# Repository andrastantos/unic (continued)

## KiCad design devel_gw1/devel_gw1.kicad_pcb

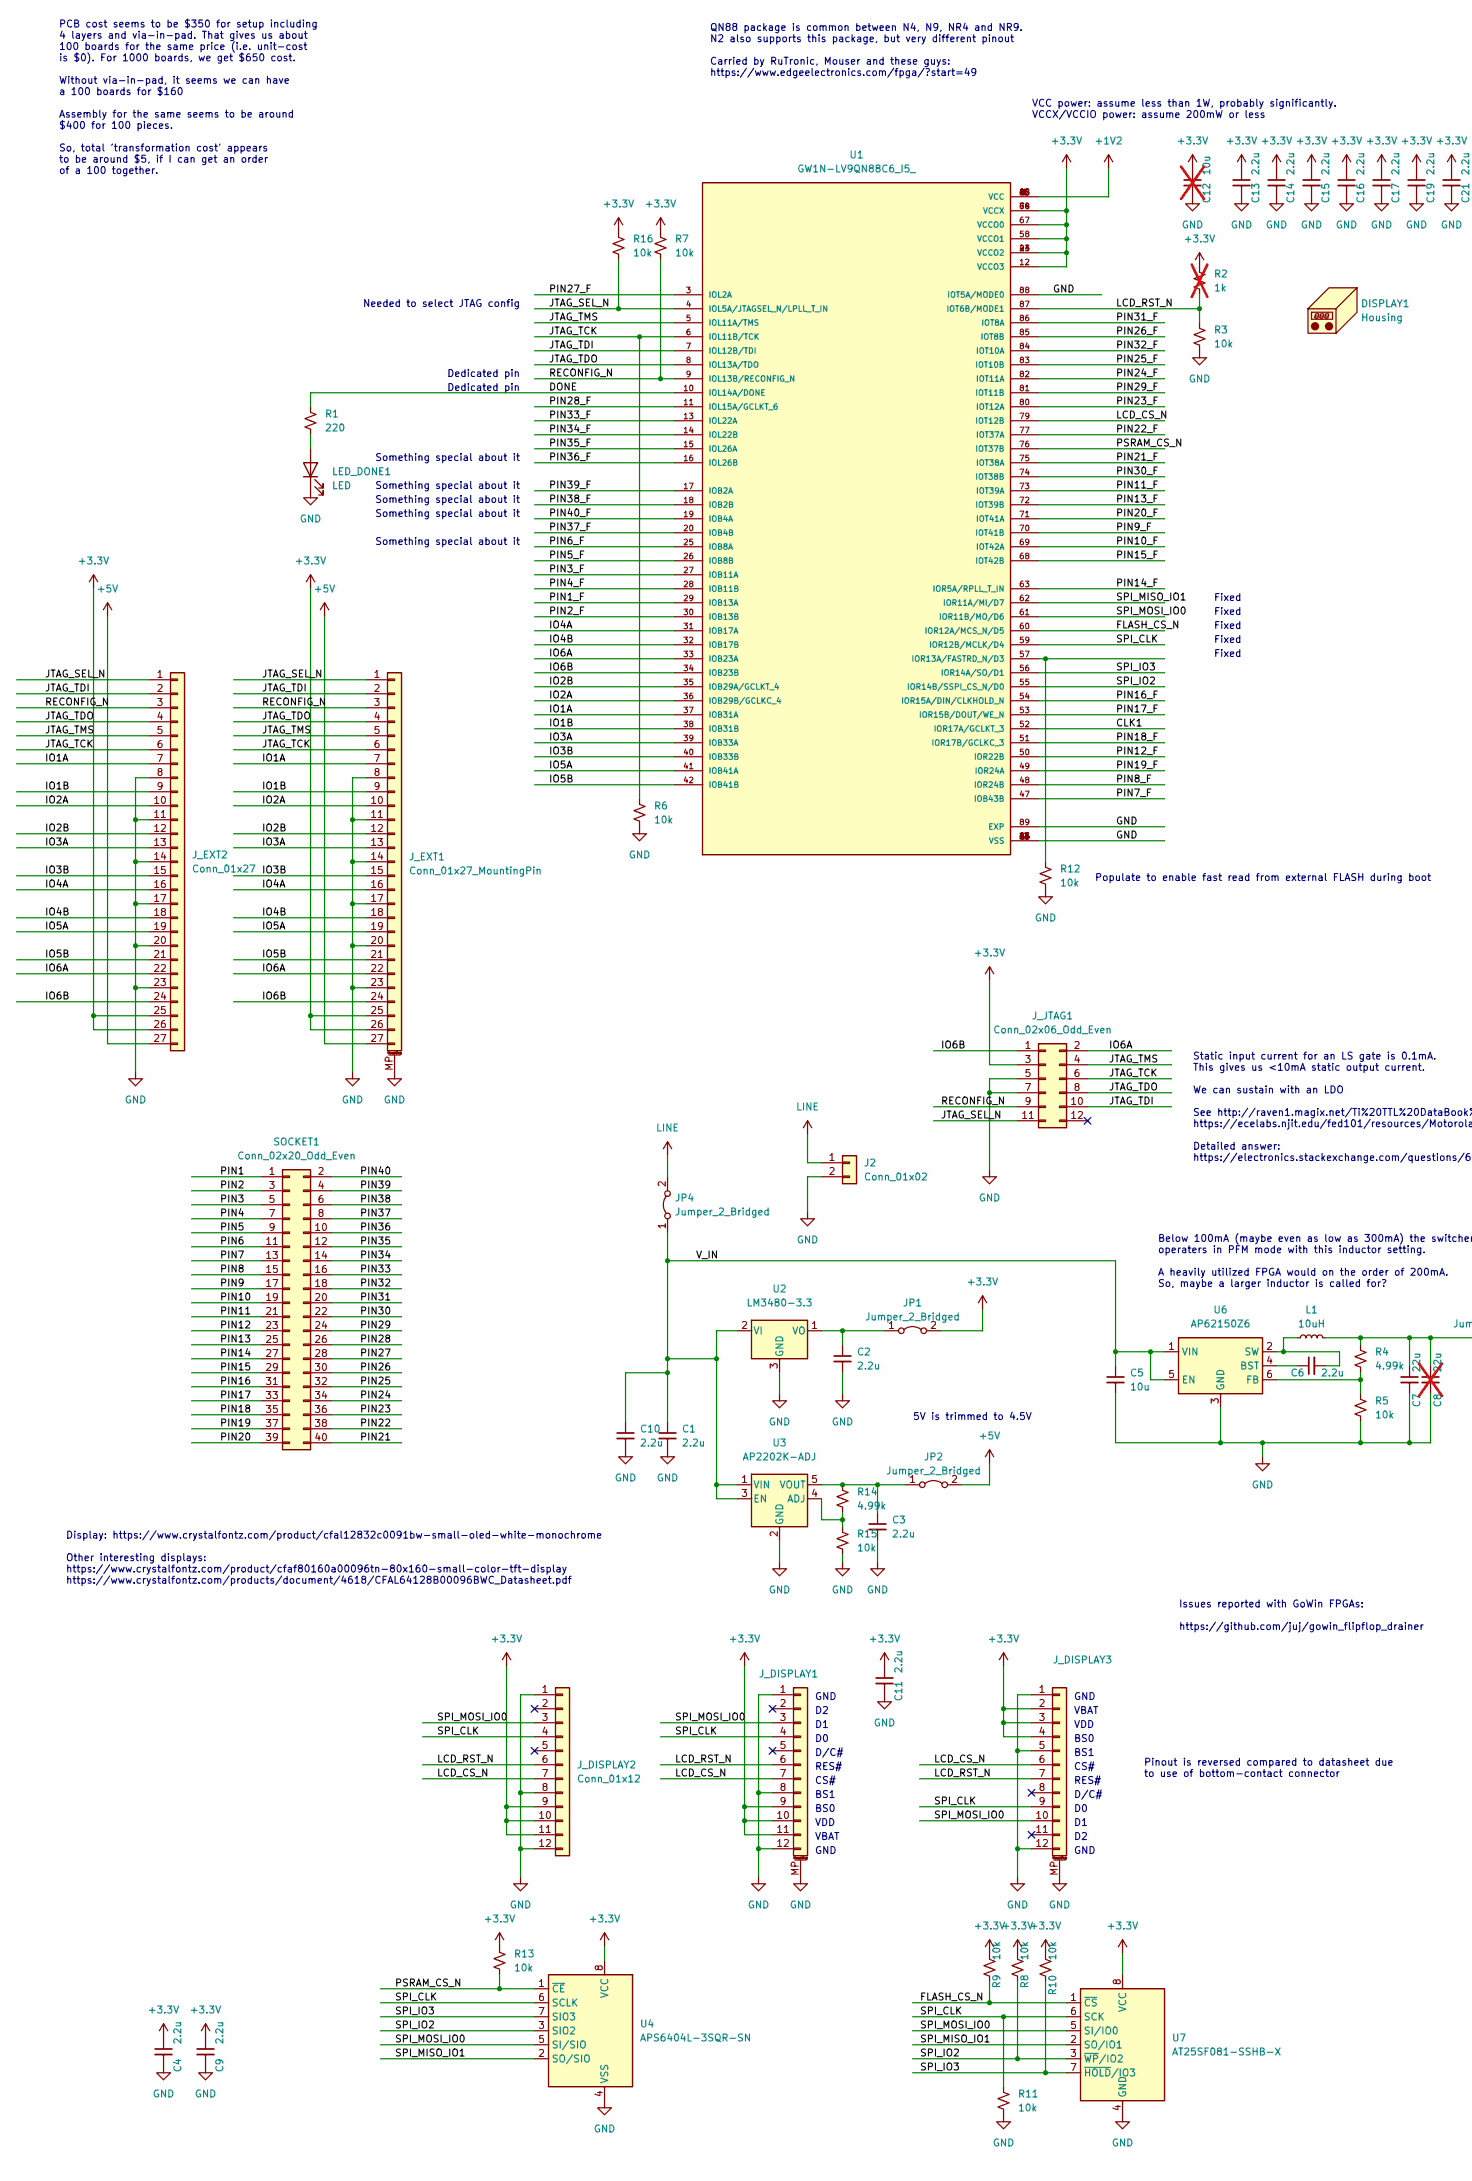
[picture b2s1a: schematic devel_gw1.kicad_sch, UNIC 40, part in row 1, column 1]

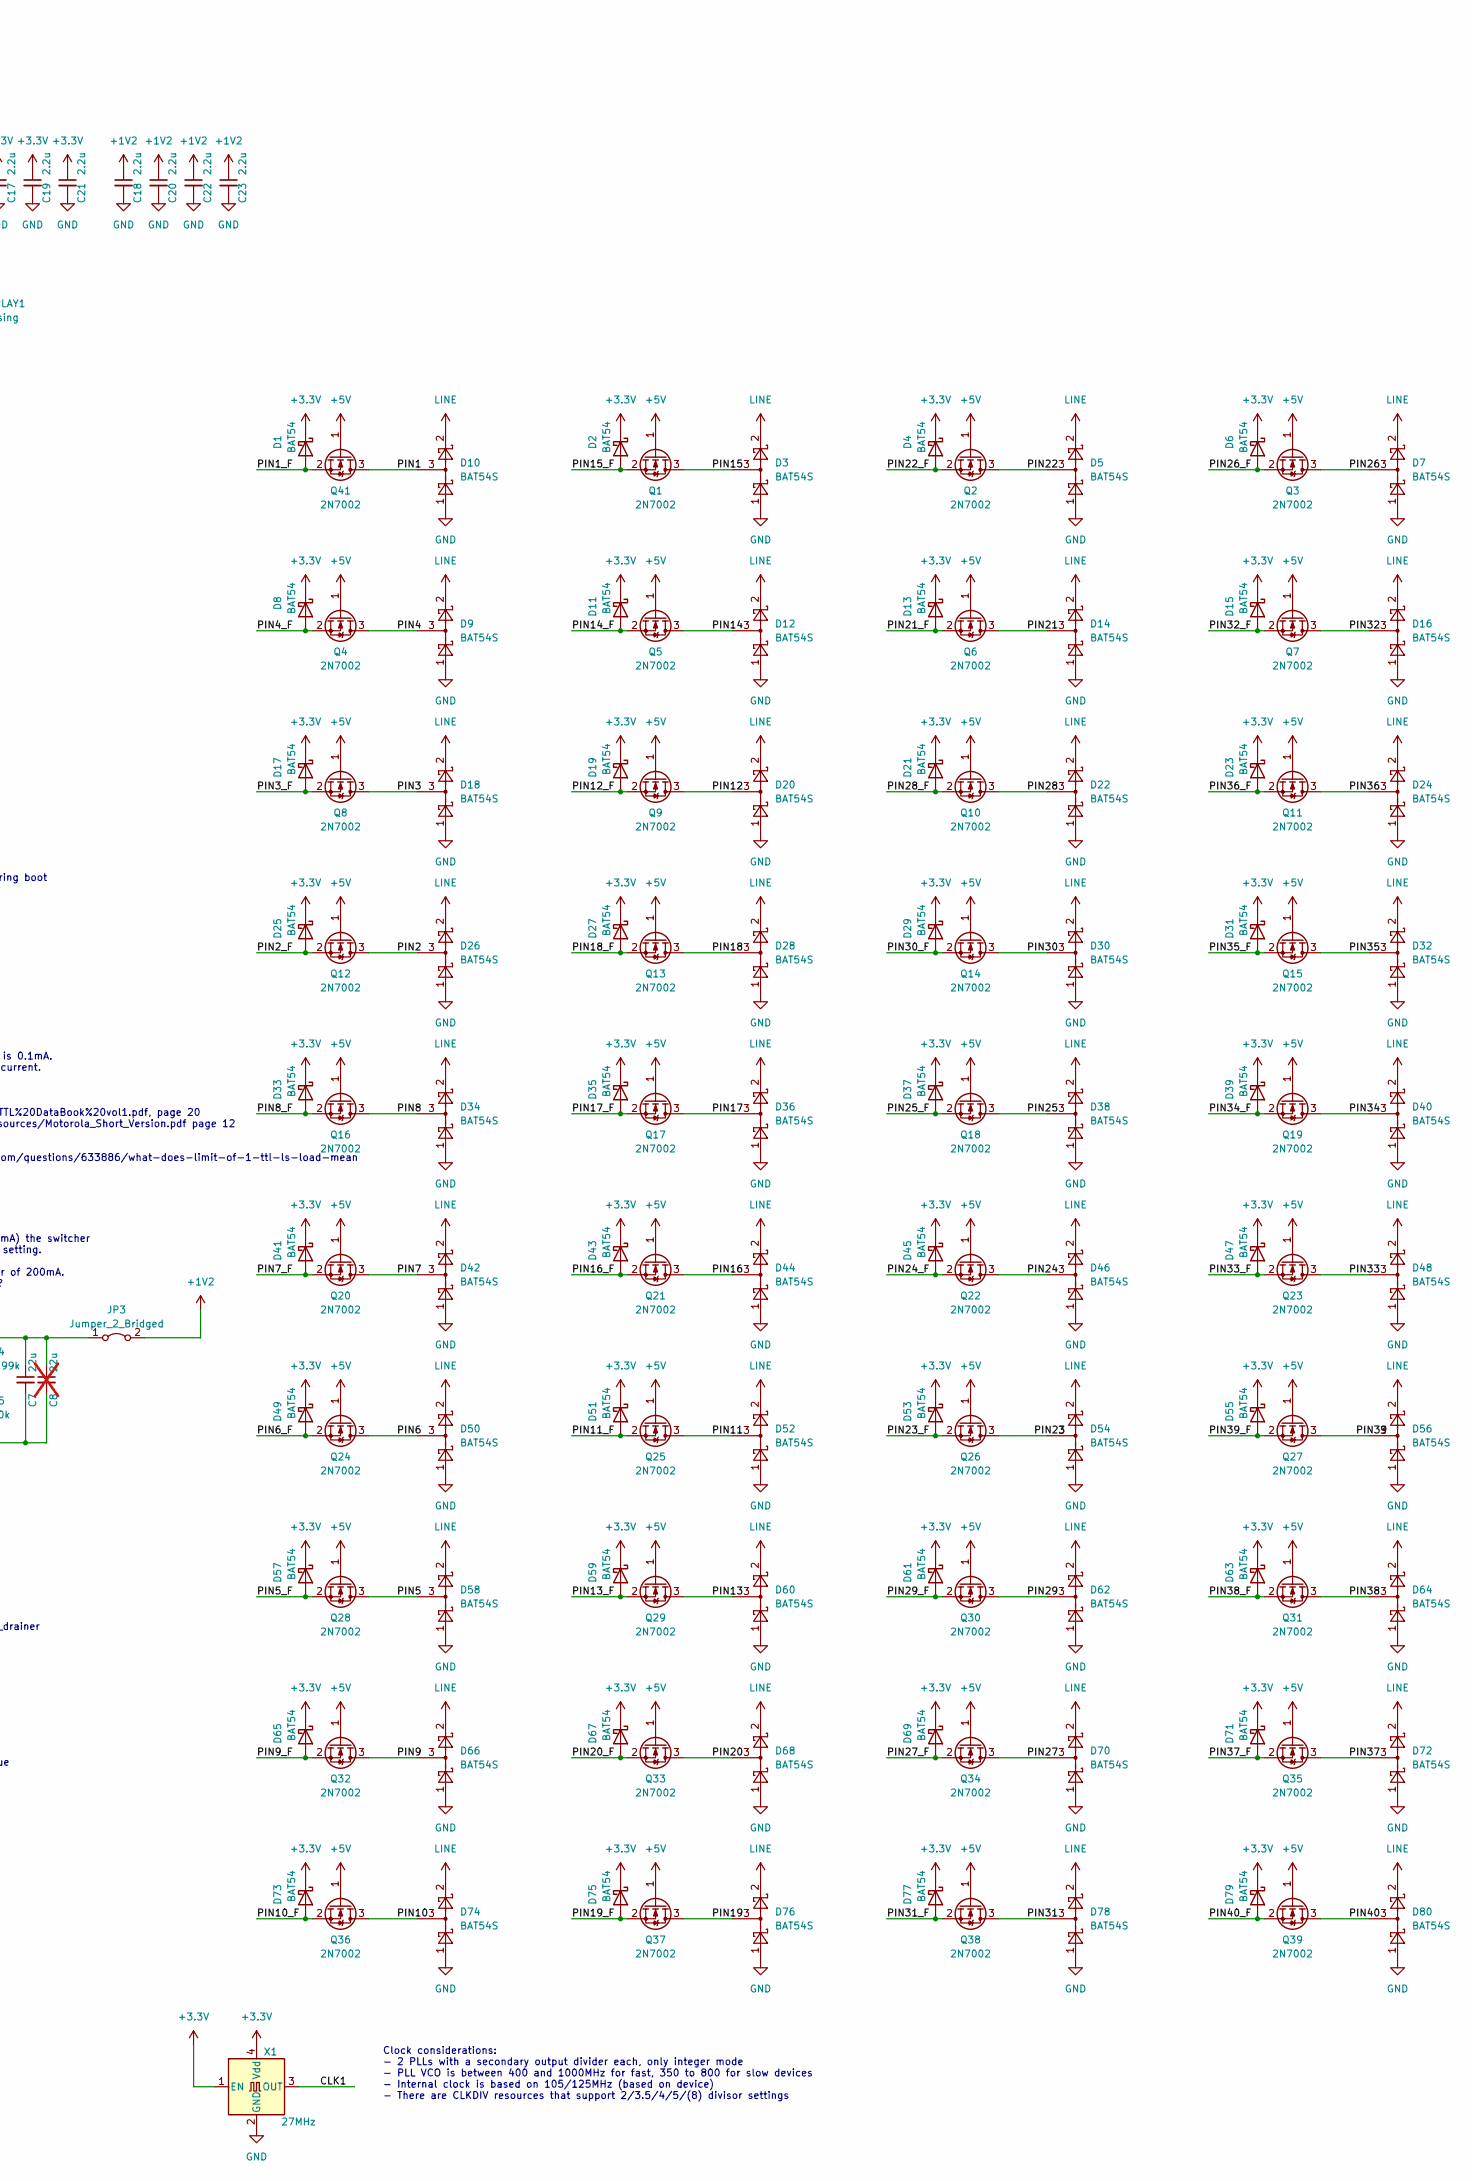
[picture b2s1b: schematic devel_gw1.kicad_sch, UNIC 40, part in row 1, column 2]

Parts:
C1, C2, C3, C4, C6, C9, C10, C11, C13, C14, C15, C16, C17, C18, C19, C20, C21, C22, C23: 2.2u; C_0402_1005Metric_Pad0.74x0.62mm_HandSolder
C5: 10u; C_0805_2012Metric_Pad1.18x1.45mm_HandSolder
C7: 22u; C_0805_2012Metric_Pad1.18x1.45mm_HandSolder
C8: 22u; C_0805_2012Metric_Pad1.18x1.45mm_HandSolder; not fitted
C12: 10u; C_0805_2012Metric_Pad1.18x1.45mm_HandSolder; not fitted
D1, D2, D4, D6, D8, D11, D13, D15, D17, D19, D21, D23, D25, D27, D29, D31, D33, D35, D37, D39, D41, D43, D45, D47, D49, D51, D53, D55, D57, D59, D61, D63, D65, D67, D69, D71, D73, D75, D77, D79: BAT54; SOT-23
D3, D5, D7, D9, D10, D12, D14, D16, D18, D20, D22, D24, D26, D28, D30, D32, D34, D36, D38, D40, D42, D44, D46, D48, D50, D52, D54, D56, D58, D60, D62, D64, D66, D68, D70, D72, D74, D76, D78, D80: BAT54S; SOT-23
DISPLAY1: Housing; CFAL12832C-0091B-W_A
J2: Conn_01x02; PinHeader_1x02_P2.54mm_Vertical
JP1, JP2, JP3, JP4: Jumper_2_Bridged; PinHeader_1x02_P2.54mm_Vertical
J_DISPLAY1: Conn_01x12_MountingPin; CF4212FH0R0-05-NH
J_DISPLAY2: Conn_01x12; PinHeader_1x12_P2.54mm_Vertical
J_DISPLAY3: Conn_01x12_MountingPin; CF31121D0R0-05-NH
J_EXT1: Conn_01x27_MountingPin; Molex_502598-2793_2Rows-23P~0.60mm_Horizontal
J_EXT2: Conn_01x27; PinHeader_2x14_P2.54mm_Vertical
J_JTAG1: Conn_02x06_Odd_Even; PinHeader_2x06_P1.27mm_Vertical_SMD
L1: 10uH; L_1008_2520Metric_Pad1.43x2.20mm_HandSolder
LED_DONE1: LED; LED_0402_1005Metric_Pad0.77x0.64mm_HandSolder
Q1, Q2, Q3, Q4, Q5, Q6, Q7, Q8, Q9, Q10, Q11, Q12, Q13, Q14, Q15, Q16, Q17, Q18, Q19, Q20, Q21, Q22, Q23, Q24, Q25, Q26, Q27, Q28, Q29, Q30, Q31, Q32, Q33, Q34, Q35, Q36, Q37, Q38, Q39, Q41: 2N7002; SOT-23
R1: 220; R_0402_1005Metric_Pad0.72x0.64mm_HandSolder
R2: 1k; R_0402_1005Metric_Pad0.72x0.64mm_HandSolder; not fitted
R3, R5, R6, R7, R8, R9, R10, R11, R12, R13, R15, R16: 10k; R_0402_1005Metric_Pad0.72x0.64mm_HandSolder
R4, R14: 4.99k; R_0402_1005Metric_Pad0.72x0.64mm_HandSolder
SOCKET1: Conn_02x20_Odd_Even; PinSocket_2x20_P2.54mm_Horizontal
U1: GW1N-LV9QN88C6_I5_; QFN40P1000X1000X95-89N_hand_solder; PARTREV UG103-2.3E
U2: LM3480-3.3; SOT-23
U3: AP2202K-ADJ; SOT-23-5
U4: APS6404L-3SQR-SN; SOIC-8_3.9x4.9mm_P1.27mm
U6: AP62150Z6; SOT-563
U7: AT25SF081-SSHB-X; SOIC-8_3.9x4.9mm_P1.27mm
X1: 27MHz; Oscillator_SMD_Abracon_ASE-4Pin_3.2x2.5mm

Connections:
+1V2: C18.1, C20.1, C22.1, C23.1, JP3.2 (B), U1.1 (VCC), U1.22 (VCC), U1.45 (VCC), U1.66 (VCC)
+3V3: C4.1, C9.1, C11.1, C12.1, C13.1, C14.1, C15.1, C16.1, C17.1, C19.1, C21.1, D1.3 (K), D2.3 (K), D4.3 (K), D6.3 (K), D8.3 (K), D11.3 (K), D13.3 (K), D15.3 (K), D17.3 (K), D19.3 (K), D21.3 (K), D23.3 (K), D25.3 (K), D27.3 (K), D29.3 (K), D31.3 (K), D33.3 (K), D35.3 (K), D37.3 (K), D39.3 (K), D41.3 (K), D43.3 (K), D45.3 (K), D47.3 (K), D49.3 (K), D51.3 (K), D53.3 (K), D55.3 (K), D57.3 (K), D59.3 (K), D61.3 (K), D63.3 (K), D65.3 (K), D67.3 (K), D69.3 (K), D71.3 (K), D73.3 (K), D75.3 (K), D77.3 (K), D79.3 (K), JP1.2 (B), J_DISPLAY1.9, J_DISPLAY1.10, J_DISPLAY1.11, J_DISPLAY2.9, J_DISPLAY2.10, J_DISPLAY2.11, J_DISPLAY3.2, J_DISPLAY3.3, J_DISPLAY3.4, J_EXT1.25, J_EXT1.26, J_EXT2.25, J_EXT2.26, J_JTAG1.3, R2.1, R7.1, R8.1, R9.1, R10.1, R13.1, R16.1, U1.12 (VCCO3), U1.23 (VCCO2), U1.44 (VCCO2), U1.58 (VCCO1), U1.64 (VCCX), U1.67 (VCCO0), U1.78 (VCCX), U4.8 (VCC), U7.8 (VCC), X1.1 (EN), X1.4 (Vdd)
+5V: JP2.2 (B), J_EXT1.27, J_EXT2.27, Q1.1 (G), Q2.1 (G), Q3.1 (G), Q4.1 (G), Q5.1 (G), Q6.1 (G), Q7.1 (G), Q8.1 (G), Q9.1 (G), Q10.1 (G), Q11.1 (G), Q12.1 (G), Q13.1 (G), Q14.1 (G), Q15.1 (G), Q16.1 (G), Q17.1 (G), Q18.1 (G), Q19.1 (G), Q20.1 (G), Q21.1 (G), Q22.1 (G), Q23.1 (G), Q24.1 (G), Q25.1 (G), Q26.1 (G), Q27.1 (G), Q28.1 (G), Q29.1 (G), Q30.1 (G), Q31.1 (G), Q32.1 (G), Q33.1 (G), Q34.1 (G), Q35.1 (G), Q36.1 (G), Q37.1 (G), Q38.1 (G), Q39.1 (G), Q41.1 (G)
/CLK1: U1.52 (IOR17A/GCLKT_3), X1.3 (OUT)
/DONE: R1.1, U1.10 (IOL14A/DONE)
/FLASH_CS_N: R9.2, U1.60 (IOR12A/MCS_N/D5), U7.1 (~CS)
/IO1A: J_EXT1.7, J_EXT2.7, U1.37 (IOB31A)
/IO1B: J_EXT1.9, J_EXT2.9, U1.38 (IOB31B)
/IO2A: J_EXT1.10, J_EXT2.10, U1.36 (IOB29B/GCLKC_4)
/IO2B: J_EXT1.12, J_EXT2.12, U1.35 (IOB29A/GCLKT_4)
/IO3A: J_EXT1.13, J_EXT2.13, U1.39 (IOB33A)
/IO3B: J_EXT1.15, J_EXT2.15, U1.40 (IOB33B)
/IO4A: J_EXT1.16, J_EXT2.16, U1.31 (IOB17A)
/IO4B: J_EXT1.18, J_EXT2.18, U1.32 (IOB17B)
/IO5A: J_EXT1.19, J_EXT2.19, U1.41 (IOB41A)
/IO5B: J_EXT1.21, J_EXT2.21, U1.42 (IOB41B)
/IO6A: J_EXT1.22, J_EXT2.22, J_JTAG1.2, U1.33 (IOB23A)
/IO6B: J_EXT1.24, J_EXT2.24, J_JTAG1.1, U1.34 (IOB23B)
/JTAG_SEL_N: J_EXT1.1, J_EXT2.1, J_JTAG1.11, R16.2, U1.4 (IOL5A/JTAGSEL_N/LPLL_T_IN)
/JTAG_TCK: J_EXT1.6, J_EXT2.6, J_JTAG1.6, R6.1, U1.6 (IOL11B/TCK)
/JTAG_TDI: J_EXT1.2, J_EXT2.2, J_JTAG1.10, U1.7 (IOL12B/TDI)
/JTAG_TDO: J_EXT1.4, J_EXT2.4, J_JTAG1.8, U1.8 (IOL13A/TDO)
/JTAG_TMS: J_EXT1.5, J_EXT2.5, J_JTAG1.4, U1.5 (IOL11A/TMS)
/LCD_CS_N: J_DISPLAY1.7, J_DISPLAY2.7, J_DISPLAY3.6, U1.79 (IOT12B)
/LCD_RST_N: J_DISPLAY1.6, J_DISPLAY2.6, J_DISPLAY3.7, R2.2, R3.1, U1.87 (IOT6B/MODE1)
/PIN1: D10.3, Q41.3 (D), SOCKET1.1
/PIN1_F: D1.1 (A), Q41.2 (S), U1.29 (IOB13A)
/PIN2: D26.3, Q12.3 (D), SOCKET1.3
/PIN2_F: D25.1 (A), Q12.2 (S), U1.30 (IOB13B)
/PIN3: D18.3, Q8.3 (D), SOCKET1.5
/PIN3_F: D17.1 (A), Q8.2 (S), U1.27 (IOB11A)
/PIN4: D9.3, Q4.3 (D), SOCKET1.7
/PIN4_F: D8.1 (A), Q4.2 (S), U1.28 (IOB11B)
/PIN5: D58.3, Q28.3 (D), SOCKET1.9
/PIN5_F: D57.1 (A), Q28.2 (S), U1.26 (IOB8B)
/PIN6: D50.3, Q24.3 (D), SOCKET1.11
/PIN6_F: D49.1 (A), Q24.2 (S), U1.25 (IOB8A)
/PIN7: D42.3, Q20.3 (D), SOCKET1.13
/PIN7_F: D41.1 (A), Q20.2 (S), U1.47 (IOB43B)
/PIN8: D34.3, Q16.3 (D), SOCKET1.15
/PIN8_F: D33.1 (A), Q16.2 (S), U1.48 (IOR24B)
/PIN9: D66.3, Q32.3 (D), SOCKET1.17
/PIN9_F: D65.1 (A), Q32.2 (S), U1.70 (IOT41B)
/PIN10: D74.3, Q36.3 (D), SOCKET1.19
/PIN10_F: D73.1 (A), Q36.2 (S), U1.69 (IOT42A)
/PIN11: D52.3, Q25.3 (D), SOCKET1.21
/PIN11_F: D51.1 (A), Q25.2 (S), U1.73 (IOT39A)
/PIN12: D20.3, Q9.3 (D), SOCKET1.23
/PIN12_F: D19.1 (A), Q9.2 (S), U1.50 (IOR22B)
/PIN13: D60.3, Q29.3 (D), SOCKET1.25
/PIN13_F: D59.1 (A), Q29.2 (S), U1.72 (IOT39B)
/PIN14: D12.3, Q5.3 (D), SOCKET1.27
/PIN14_F: D11.1 (A), Q5.2 (S), U1.63 (IOR5A/RPLL_T_IN)
/PIN15: D3.3, Q1.3 (D), SOCKET1.29
/PIN15_F: D2.1 (A), Q1.2 (S), U1.68 (IOT42B)
/PIN16: D44.3, Q21.3 (D), SOCKET1.31
/PIN16_F: D43.1 (A), Q21.2 (S), U1.54 (IOR15A/DIN/CLKHOLD_N)
/PIN17: D36.3, Q17.3 (D), SOCKET1.33
/PIN17_F: D35.1 (A), Q17.2 (S), U1.53 (IOR15B/DOUT/WE_N)
/PIN18: D28.3, Q13.3 (D), SOCKET1.35
/PIN18_F: D27.1 (A), Q13.2 (S), U1.51 (IOR17B/GCLKC_3)
/PIN19: D76.3, Q37.3 (D), SOCKET1.37
/PIN19_F: D75.1 (A), Q37.2 (S), U1.49 (IOR24A)
/PIN20: D68.3, Q33.3 (D), SOCKET1.39
/PIN20_F: D67.1 (A), Q33.2 (S), U1.71 (IOT41A)
/PIN21: D14.3, Q6.3 (D), SOCKET1.40
/PIN21_F: D13.1 (A), Q6.2 (S), U1.75 (IOT38A)
/PIN22: D5.3, Q2.3 (D), SOCKET1.38
/PIN22_F: D4.1 (A), Q2.2 (S), U1.77 (IOT37A)
/PIN23: D54.3, Q26.3 (D), SOCKET1.36
/PIN23_F: D53.1 (A), Q26.2 (S), U1.80 (IOT12A)
/PIN24: D46.3, Q22.3 (D), SOCKET1.34
/PIN24_F: D45.1 (A), Q22.2 (S), U1.82 (IOT11A)
/PIN25: D38.3, Q18.3 (D), SOCKET1.32
/PIN25_F: D37.1 (A), Q18.2 (S), U1.83 (IOT10B)
/PIN26: D7.3, Q3.3 (D), SOCKET1.30
/PIN26_F: D6.1 (A), Q3.2 (S), U1.85 (IOT8B)
/PIN27: D70.3, Q34.3 (D), SOCKET1.28
/PIN27_F: D69.1 (A), Q34.2 (S), U1.3 (IOL2A)
/PIN28: D22.3, Q10.3 (D), SOCKET1.26
/PIN28_F: D21.1 (A), Q10.2 (S), U1.11 (IOL15A/GCLKT_6)
/PIN29: D62.3, Q30.3 (D), SOCKET1.24
/PIN29_F: D61.1 (A), Q30.2 (S), U1.81 (IOT11B)
/PIN30: D30.3, Q14.3 (D), SOCKET1.22
/PIN30_F: D29.1 (A), Q14.2 (S), U1.74 (IOT38B)
/PIN31: D78.3, Q38.3 (D), SOCKET1.20
/PIN31_F: D77.1 (A), Q38.2 (S), U1.86 (IOT8A)
/PIN32: D16.3, Q7.3 (D), SOCKET1.18
/PIN32_F: D15.1 (A), Q7.2 (S), U1.84 (IOT10A)
/PIN33: D48.3, Q23.3 (D), SOCKET1.16
/PIN33_F: D47.1 (A), Q23.2 (S), U1.13 (IOL22A)
/PIN34: D40.3, Q19.3 (D), SOCKET1.14
/PIN34_F: D39.1 (A), Q19.2 (S), U1.14 (IOL22B)
/PIN35: D32.3, Q15.3 (D), SOCKET1.12
/PIN35_F: D31.1 (A), Q15.2 (S), U1.15 (IOL26A)
/PIN36: D24.3, Q11.3 (D), SOCKET1.10
/PIN36_F: D23.1 (A), Q11.2 (S), U1.16 (IOL26B)
/PIN37: D72.3, Q35.3 (D), SOCKET1.8
/PIN37_F: D71.1 (A), Q35.2 (S), U1.20 (IOB4B)
/PIN38: D64.3, Q31.3 (D), SOCKET1.6
/PIN38_F: D63.1 (A), Q31.2 (S), U1.18 (IOB2B)
/PIN39: D56.3, Q27.3 (D), SOCKET1.4
/PIN39_F: D55.1 (A), Q27.2 (S), U1.17 (IOB2A)
/PIN40: D80.3, Q39.3 (D), SOCKET1.2
/PIN40_F: D79.1 (A), Q39.2 (S), U1.19 (IOB4A)
/PSRAM_CS_N: R13.2, U1.76 (IOT37B), U4.1 (~CE)
/RECONFIG_N: J_EXT1.3, J_EXT2.3, J_JTAG1.9, R7.2, U1.9 (IOL13B/RECONFIG_N)
/SPI_CLK: J_DISPLAY1.4, J_DISPLAY2.4, J_DISPLAY3.9, R11.1, U1.59 (IOR12B/MCLK/D4), U4.6 (SCLK), U7.6 (SCK)
/SPI_IO2: R8.2, U1.55 (IOR14B/SSPI_CS_N/D0), U4.3 (SIO2), U7.3 (~WP/IO2)
/SPI_IO3: R10.2, U1.56 (IOR14A/SO/D1), U4.7 (SIO3), U7.7 (~HOLD/IO3)
/SPI_MISO_IO1: U1.62 (IOR11A/MI/D7), U4.2 (SO/SIO), U7.2 (SO/IO1)
/SPI_MOSI_IO0: J_DISPLAY1.3, J_DISPLAY2.3, J_DISPLAY3.10, U1.61 (IOR11B/MO/D6), U4.5 (SI/SIO), U7.5 (SI/IO0)
/V_IN: C1.1, C5.1, C10.1, JP4.1 (A), U2.2 (VI), U3.1 (VIN), U3.3 (EN), U6.1 (VIN), U6.5 (EN)
GND: C1.2, C2.2, C3.2, C4.2, C5.2, C7.2, C8.2, C9.2, C10.2, C11.2, C12.2, C13.2, C14.2, C15.2, C16.2, C17.2, C18.2, C19.2, C20.2, C21.2, C22.2, C23.2, D3.1, D5.1, D7.1, D9.1, D10.1, D12.1, D14.1, D16.1, D18.1, D20.1, D22.1, D24.1, D26.1, D28.1, D30.1, D32.1, D34.1, D36.1, D38.1, D40.1, D42.1, D44.1, D46.1, D48.1, D50.1, D52.1, D54.1, D56.1, D58.1, D60.1, D62.1, D64.1, D66.1, D68.1, D70.1, D72.1, D74.1, D76.1, D78.1, D80.1, J2.2, J_DISPLAY1.1, J_DISPLAY1.8, J_DISPLAY1.12, J_DISPLAY1.MP (MountPin), J_DISPLAY2.1, J_DISPLAY2.8, J_DISPLAY2.12, J_DISPLAY3.1, J_DISPLAY3.5, J_DISPLAY3.12, J_DISPLAY3.MP (MountPin), J_EXT1.8, J_EXT1.11, J_EXT1.14, J_EXT1.17, J_EXT1.20, J_EXT1.23, J_EXT1.MP (MountPin), J_EXT2.8, J_EXT2.11, J_EXT2.14, J_EXT2.17, J_EXT2.20, J_EXT2.23, J_JTAG1.5, J_JTAG1.7, LED_DONE1.1 (K), R3.2, R5.2, R6.2, R11.2, R12.2, R15.2, U1.2 (VSS), U1.21 (VSS), U1.24 (VSS), U1.43 (VSS), U1.46 (VSS), U1.65 (VSS), U1.88 (IOT5A/MODE0), U1.89 (EXP), U2.3 (GND), U3.2 (GND), U4.4 (VSS), U6.3 (GND), U7.4 (GND), X1.2 (GND)
LINE: D3.2, D5.2, D7.2, D9.2, D10.2, D12.2, D14.2, D16.2, D18.2, D20.2, D22.2, D24.2, D26.2, D28.2, D30.2, D32.2, D34.2, D36.2, D38.2, D40.2, D42.2, D44.2, D46.2, D48.2, D50.2, D52.2, D54.2, D56.2, D58.2, D60.2, D62.2, D64.2, D66.2, D68.2, D70.2, D72.2, D74.2, D76.2, D78.2, D80.2, J2.1, JP4.2 (B)
unnamed: C2.1, JP1.1 (A), U2.1 (VO)
unnamed: C3.1, JP2.1 (A), R14.1, U3.5 (VOUT)
unnamed: C7.1, C8.1, JP3.1 (A), L1.2, R4.1
unnamed: LED_DONE1.2 (A), R1.2
unnamed: R12.1, U1.57 (IOR13A/FASTRD_N/D3)
unnamed: R14.2, R15.1, U3.4 (ADJ)
unnamed: C6.1, U6.4 (BST)
unnamed: R4.2, R5.1, U6.6 (FB)
unnamed: C6.2, L1.1, U6.2 (SW)

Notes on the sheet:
BS0
Issues reported with GoWin FPGAs: https://github.com/juj/gowin_flipflop_drainer
D/C#
Populate to enable fast read from external FLASH during boot
VBAT
Fixed
Something special about it
BS1
PCB cost seems to be $350 for setup including 4 layers and via-in-pad. That gives us about 100 boards for the same price (i.e. unit-cost is $0). For 1000 boards, we get $650 cost. Without via-in-pad, it seems we can have a 100 boards for $160 Assembly for the same seems to be around $400 for 100 pi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
RES#
GND
VCC power: assume less than 1W, probably significantly. VCCX/VCCIO power: assume 200mW or less
CS#
Clock considerations: - 2 PLLs with a secondary output divider each, only integer mode - PLL VCO is between 400 and 1000MHz for fast, 350 to 800 for slow devices - Internal clock is based on 105/125MHz (based on device) - There are CLKDIV resources that support 2/3.5/4/5/(8) divisor settings
Static input current for an LS gate is 0.1mA. This gives us <10mA static output current. We can sustain with an LDO See http://raven1.magix.net/Ti%20TTL%20DataBook%20vol1.pdf, page 20 https://ecelabs.njit.edu/fed101/resources/Motorola_Short_Version.pdf page 12 Detailed answer: https://electronics.s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
Dedicated pin
Pinout is reversed compared to datasheet due to use of bottom-contact connector
Needed to select JTAG config
Below 100mA (maybe even as low as 300mA) the switcher operaters in PFM mode with this inductor setting. A heavily utilized FPGA would on the order of 200mA. So, maybe a larger inductor is called for?
QN88 package is common between N4, N9, NR4 and NR9. N2 also supports this package, but very different pinout Carried by RuTronic, Mouser and these guys: https://www.edgeelectronics.com/fpga/?start=49
5V is trimmed to 4.5V
Display: https://www.crystalfontz.com/product/cfal12832c0091bw-small-oled-white-monochrome Other interesting displays: https://www.crystalfontz.com/product/cfaf80160a00096tn-80x160-small-color-tft-display https://www.crystalfontz.com/products/document/4618/CFAL64128B00096BWC_Datasheet.pdf
VDD

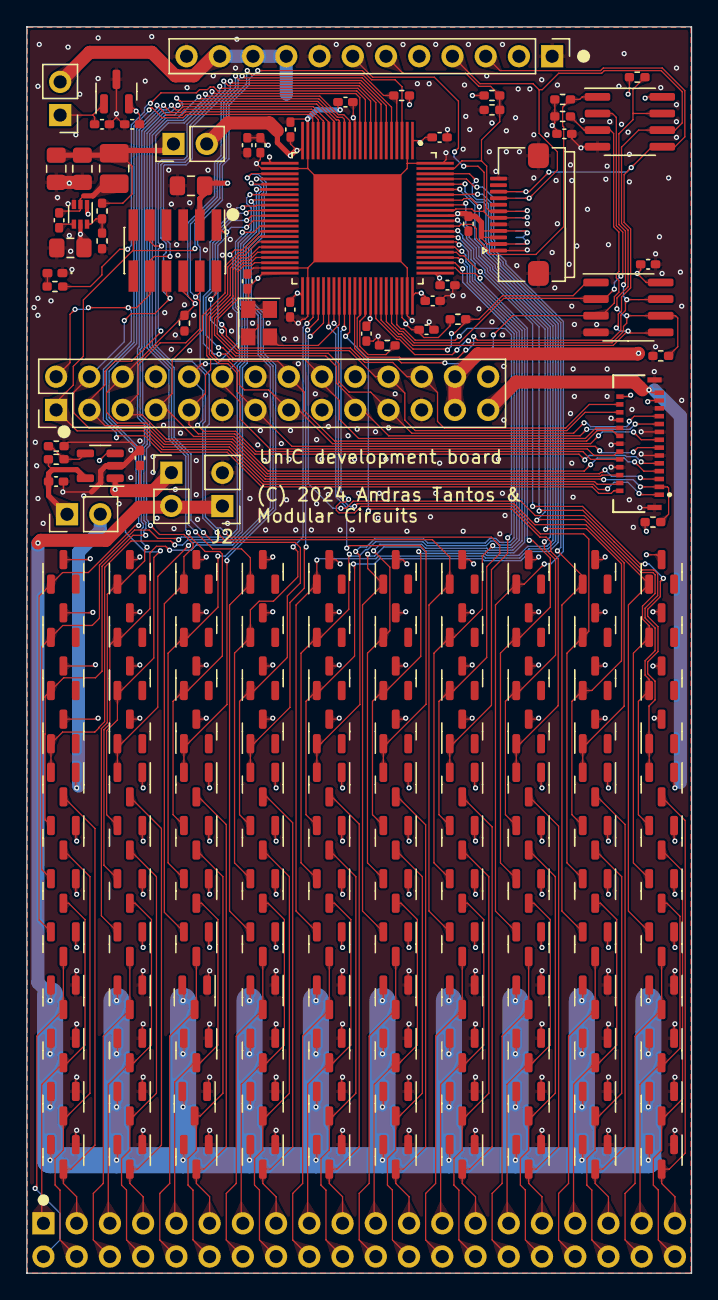
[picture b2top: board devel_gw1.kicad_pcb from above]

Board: 2 copper layers, 50.8 x 95.2 mm, 181 parts (1 on the bottom side), 124 nets.

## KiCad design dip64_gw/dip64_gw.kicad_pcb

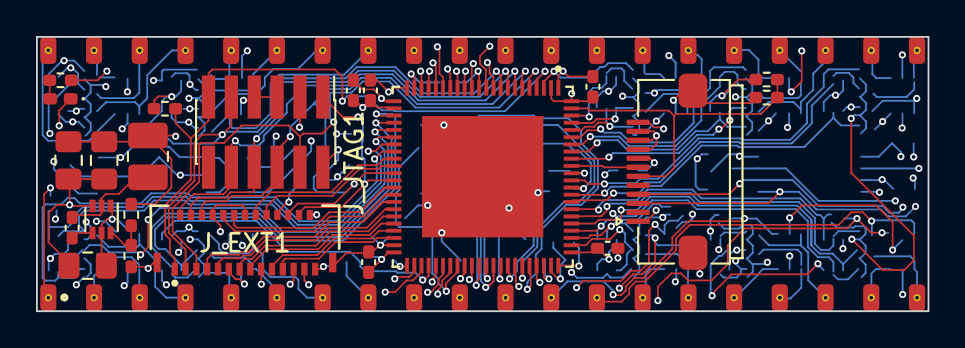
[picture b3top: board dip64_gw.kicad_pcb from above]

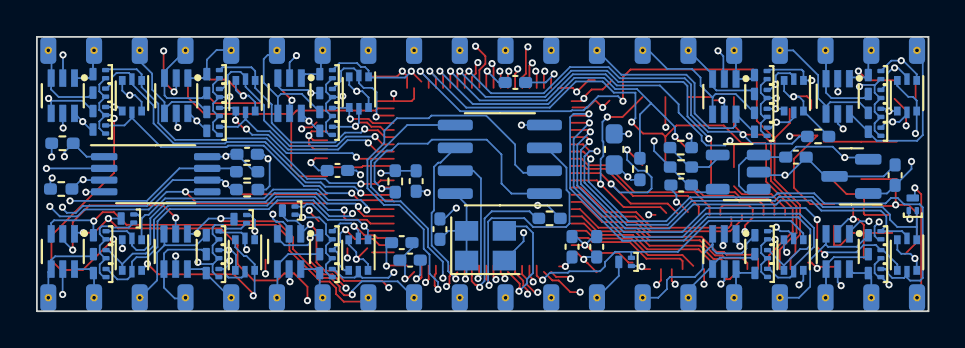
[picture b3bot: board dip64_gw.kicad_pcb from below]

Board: 4 copper layers, 49.5 x 15.2 mm, 112 parts (88 on the bottom side), 120 nets.

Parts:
C1, C2, C4, C6, C9, C11, C13, C14, C15, C16, C17, C18, C19, C20, C21, C22, C23: 0.1u; C_0402_1005Metric_Pad0.74x0.62mm_HandSolder
C3: 2.2u; C_0402_1005Metric_Pad0.74x0.62mm_HandSolder
C5: 10u; C_0805_2012Metric_Pad1.18x1.45mm_HandSolder
C7, C8: 22u; C_0805_2012Metric_Pad1.18x1.45mm_HandSolder
C12: 10u; C_0603_1608Metric_Pad1.08x0.95mm_HandSolder
D1, D2, D3, D4, D5, D6, D7, D8, D9, D11: BAT54DF; SOT65P210X110-6N
D21, D22, D23, D24, D25, D26, D27, D28, D29, D30: BAT54CV; SOT-666
DISPLAY1: Housing; CFAL12832C-0091B-W_A
J_DISPLAY1: Conn_01x12_MountingPin; CF31121D0R0-05-NH
J_EXT1: Conn_01x27_MountingPin; Molex_502598-2793_2Rows-23P~0.60mm_Horizontal
J_JTAG1: Conn_02x06_Odd_Even; PinHeader_2x06_P1.27mm_Vertical_SMD
L1: 3.3uH; L_1008_2520Metric_Pad1.43x2.20mm_HandSolder
LED_DONE1: LED; LED_0402_1005Metric_Pad0.77x0.64mm_HandSolder
Q1, Q2, Q3, Q4, Q5, Q6, Q7, Q8, Q9, Q10, Q11, Q12, Q13, Q14, Q15, Q16, Q17, Q18, Q19, Q20, Q21, Q22, Q23, Q24, Q25, Q26, Q27, Q28, Q29, Q30, Q31, Q32, Q33, Q34, Q35, Q36, Q37, Q38, Q39, Q40: 2N7002; SOT-883
R1: 220; R_0402_1005Metric_Pad0.72x0.64mm_HandSolder
R2: DNC; R_0402_1005Metric_Pad0.72x0.64mm_HandSolder
R3, R5, R6, R7, R8, R9, R10, R11, R12, R13, R15, R16: 10k; R_0402_1005Metric_Pad0.72x0.64mm_HandSolder
R4, R14: 4.99k; R_0402_1005Metric_Pad0.72x0.64mm_HandSolder
SOCKET1: Conn_02x20_Counter_Clockwise; DIP-40_pin_header
U1: GW1N-LV9QN88C6_I5_; QFN40P1000X1000X95-89N
U2: LM3480-3.3; SOT-23
U3: AP2202K-ADJ; SOT-23-5
U4: ESP-PSRAM32; SOIC-8_3.9x4.9mm_P1.27mm
U5: AT25SF081-XMHF-X; TSSOP-8_4.4x3mm_P0.65mm
U6: AP62150Z6; SOT-563
X1: ASE-xxxMHz; Oscillator_SMD_Abracon_ASE-4Pin_3.2x2.5mm

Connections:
+1V2: C7.1, C8.1, C18.1, C20.1, C22.1, C23.1, L1.2, R4.1, U1.1 (VCC), U1.22 (VCC), U1.45 (VCC), U1.66 (VCC)
+3V3: C2.1, C4.1, C9.1, C11.1, C12.1, C13.1, C14.1, C15.1, C16.1, C17.1, C19.1, C21.1, D21.3 (A), D21.6 (A), D22.3 (A), D22.6 (A), D23.3 (A), D23.6 (A), D24.3 (A), D24.6 (A), D25.3 (A), D25.6 (A), D26.3 (A), D26.6 (A), D27.3 (A), D27.6 (A), D28.3 (A), D28.6 (A), D29.3 (A), D29.6 (A), D30.3 (A), D30.6 (A), J_DISPLAY1.9, J_DISPLAY1.10, J_DISPLAY1.11, J_EXT1.25, J_EXT1.26, J_JTAG1.3, R2.1, R7.1, R8.1, R9.1, R10.1, R13.1, R16.1, U1.12 (VCCO3), U1.23 (VCCO2), U1.44 (VCCO2), U1.58 (VCCO1), U1.64 (VCCX), U1.67 (VCCO0), U1.78 (VCCX), U2.1 (VO), U4.8 (VCC), U5.8 (VCC), X1.1 (EN), X1.4 (Vdd)
+5V: C3.1, J_EXT1.27, Q1.1 (G), Q2.1 (G), Q3.1 (G), Q4.1 (G), Q5.1 (G), Q6.1 (G), Q7.1 (G), Q8.1 (G), Q9.1 (G), Q10.1 (G), Q11.1 (G), Q12.1 (G), Q13.1 (G), Q14.1 (G), Q15.1 (G), Q16.1 (G), Q17.1 (G), Q18.1 (G), Q19.1 (G), Q20.1 (G), Q21.1 (G), Q22.1 (G), Q23.1 (G), Q24.1 (G), Q25.1 (G), Q26.1 (G), Q27.1 (G), Q28.1 (G), Q29.1 (G), Q30.1 (G), Q31.1 (G), Q32.1 (G), Q33.1 (G), Q34.1 (G), Q35.1 (G), Q36.1 (G), Q37.1 (G), Q38.1 (G), Q39.1 (G), Q40.1 (G), R14.1, U3.5 (VOUT)
/CLK1: U1.52 (IOR17A/GCLKT_3), X1.3 (OUT)
/DONE: R1.1, U1.10 (IOL14A/DONE)
/FLASH_CS_N: R9.2, U1.60 (IOR12A/MCS_N/D5), U5.1 (~CS)
/IO1A: J_EXT1.7, U1.37 (IOB31A)
/IO1B: J_EXT1.9, U1.38 (IOB31B)
/IO2A: J_EXT1.10, U1.36 (IOB29B/GCLKC_4)
/IO2B: J_EXT1.12, U1.35 (IOB29A/GCLKT_4)
/IO3A: J_EXT1.13, U1.39 (IOB33A)
/IO3B: J_EXT1.15, U1.40 (IOB33B)
/IO4A: J_EXT1.16, U1.31 (IOB17A)
/IO4B: J_EXT1.18, U1.32 (IOB17B)
/IO5A: J_EXT1.19, U1.41 (IOB41A)
/IO5B: J_EXT1.21, U1.42 (IOB41B)
/IO6A: J_EXT1.22, J_JTAG1.2, U1.33 (IOB23A)
/IO6B: J_EXT1.24, J_JTAG1.1, U1.34 (IOB23B)
/JTAG_SEL_N: J_EXT1.1, J_JTAG1.11, R16.2, U1.4 (IOL5A/JTAGSEL_N/LPLL_T_IN)
/JTAG_TCK: J_EXT1.6, J_JTAG1.6, R6.1, U1.6 (IOL11B/TCK)
/JTAG_TDI: J_EXT1.2, J_JTAG1.10, U1.7 (IOL12B/TDI)
/JTAG_TDO: J_EXT1.4, J_JTAG1.8, U1.8 (IOL13A/TDO)
/JTAG_TMS: J_EXT1.5, J_JTAG1.4, U1.5 (IOL11A/TMS)
/LCD_CS_N: J_DISPLAY1.7, U1.79 (IOT12B)
/LCD_RST_N: J_DISPLAY1.6, R2.2, R3.1, U1.87 (IOT6B/MODE1)
/PIN1: D1.1, Q1.3 (D), SOCKET1.1
/PIN1_F: D21.1 (K), Q1.2 (S), U1.29 (IOB13A)
/PIN2: D1.6, Q4.3 (D), SOCKET1.2
/PIN2_F: D21.5 (K), Q4.2 (S), U1.30 (IOB13B)
/PIN3: D1.4, Q3.3 (D), SOCKET1.3
/PIN3_F: D21.4 (K), Q3.2 (S), U1.27 (IOB11A)
/PIN4: D1.3, Q2.3 (D), SOCKET1.4
/PIN4_F: D21.2 (K), Q2.2 (S), U1.28 (IOB11B)
/PIN5: D2.6, Q8.3 (D), SOCKET1.5
/PIN5_F: D22.5 (K), Q8.2 (S), U1.26 (IOB8B)
/PIN6: D2.4, Q7.3 (D), SOCKET1.6
/PIN6_F: D22.4 (K), Q7.2 (S), U1.25 (IOB8A)
/PIN7: D2.3, Q6.3 (D), SOCKET1.7
/PIN7_F: D22.2 (K), Q6.2 (S), U1.47 (IOB43B)
/PIN8: D2.1, Q5.3 (D), SOCKET1.8
/PIN8_F: D22.1 (K), Q5.2 (S), U1.48 (IOR24B)
/PIN9: D3.1, Q9.3 (D), SOCKET1.9
/PIN9_F: D23.1 (K), Q9.2 (S), U1.70 (IOT41B)
/PIN10: D3.3, Q10.3 (D), SOCKET1.10
/PIN10_F: D23.2 (K), Q10.2 (S), U1.69 (IOT42A)
/PIN11: D5.1, Q19.3 (D), SOCKET1.11
/PIN11_F: D25.1 (K), Q19.2 (S), U1.73 (IOT39A)
/PIN12: D4.1, Q15.3 (D), SOCKET1.12
/PIN12_F: D24.1 (K), Q15.2 (S), U1.50 (IOR22B)
/PIN13: D5.3, Q20.3 (D), SOCKET1.13
/PIN13_F: D25.2 (K), Q20.2 (S), U1.72 (IOT39B)
/PIN14: D3.6, Q14.3 (D), SOCKET1.14
/PIN14_F: D23.5 (K), Q14.2 (S), U1.63 (IOR5A/RPLL_T_IN)
/PIN15: D3.4, Q13.3 (D), SOCKET1.15
/PIN15_F: D23.4 (K), Q13.2 (S), U1.68 (IOT42B)
/PIN16: D4.6, Q18.3 (D), SOCKET1.16
/PIN16_F: D24.5 (K), Q18.2 (S), U1.54 (IOR15A/DIN/CLKHOLD_N)
/PIN17: D4.4, Q17.3 (D), SOCKET1.17
/PIN17_F: D24.4 (K), Q17.2 (S), U1.53 (IOR15B/DOUT/WE_N)
/PIN18: D4.3, Q16.3 (D), SOCKET1.18
/PIN18_F: D24.2 (K), Q16.2 (S), U1.51 (IOR17B/GCLKC_3)
/PIN19: D5.6, Q22.3 (D), SOCKET1.19
/PIN19_F: D25.5 (K), Q22.2 (S), U1.49 (IOR24A)
/PIN20: D5.4, Q21.3 (D), SOCKET1.20
/PIN20_F: D25.4 (K), Q21.2 (S), U1.71 (IOT41A)
/PIN21: D11.3, Q12.3 (D), SOCKET1.21
/PIN21_F: D26.2 (K), Q12.2 (S), U1.75 (IOT38A)
/PIN22: D11.1, Q11.3 (D), SOCKET1.22
/PIN22_F: D26.1 (K), Q11.2 (S), U1.77 (IOT37A)
/PIN23: D6.4, Q27.3 (D), SOCKET1.23
/PIN23_F: D27.4 (K), Q27.2 (S), U1.80 (IOT12A)
/PIN24: D6.3, Q24.3 (D), SOCKET1.24
/PIN24_F: D27.2 (K), Q24.2 (S), U1.82 (IOT11A)
/PIN25: D6.1, Q23.3 (D), SOCKET1.25
/PIN25_F: D27.1 (K), Q23.2 (S), U1.83 (IOT10B)
/PIN26: D7.4, Q31.3 (D), SOCKET1.26
/PIN26_F: D28.4 (K), Q31.2 (S), U1.85 (IOT8B)
/PIN27: D7.1, Q29.3 (D), SOCKET1.27
/PIN27_F: D28.1 (K), Q29.2 (S), U1.3 (IOL2A)
/PIN28: D11.4, Q25.3 (D), SOCKET1.28
/PIN28_F: D26.4 (K), Q25.2 (S), U1.11 (IOL15A/GCLKT_6)
/PIN29: D6.6, Q28.3 (D), SOCKET1.29
/PIN29_F: D27.5 (K), Q28.2 (S), U1.81 (IOT11B)
/PIN30: D11.6, Q26.3 (D), SOCKET1.30
/PIN30_F: D26.5 (K), Q26.2 (S), U1.74 (IOT38B)
/PIN31: D7.3, Q30.3 (D), SOCKET1.31
/PIN31_F: D28.2 (K), Q30.2 (S), U1.86 (IOT8A)
/PIN32: D7.6, Q32.3 (D), SOCKET1.32
/PIN32_F: D28.5 (K), Q32.2 (S), U1.84 (IOT10A)
/PIN33: D8.6, Q36.3 (D), SOCKET1.33
/PIN33_F: D29.5 (K), Q36.2 (S), U1.13 (IOL22A)
/PIN34: D8.4, Q35.3 (D), SOCKET1.34
/PIN34_F: D29.4 (K), Q35.2 (S), U1.14 (IOL22B)
/PIN35: D8.3, Q34.3 (D), SOCKET1.35
/PIN35_F: D29.2 (K), Q34.2 (S), U1.15 (IOL26A)
/PIN36: D8.1, Q33.3 (D), SOCKET1.36
/PIN36_F: D29.1 (K), Q33.2 (S), U1.16 (IOL26B)
/PIN37: D9.4, Q39.3 (D), SOCKET1.37
/PIN37_F: D30.4 (K), Q39.2 (S), U1.20 (IOB4B)
/PIN38: D9.3, Q38.3 (D), SOCKET1.38
/PIN38_F: D30.2 (K), Q38.2 (S), U1.18 (IOB2B)
/PIN39: D9.1, Q37.3 (D), SOCKET1.39
/PIN39_F: D30.1 (K), Q37.2 (S), U1.17 (IOB2A)
/PIN40: D9.6, Q40.3 (D), SOCKET1.40
/PIN40_F: D30.5 (K), Q40.2 (S), U1.19 (IOB4A)
/PSRAM_CS_N: R13.2, U1.76 (IOT37B), U4.1 (~CE)
/RECONFIG_N: J_EXT1.3, J_JTAG1.9, R7.2, U1.9 (IOL13B/RECONFIG_N)
/SPI_CLK: J_DISPLAY1.4, R11.1, U1.59 (IOR12B/MCLK/D4), U4.6 (SCLK), U5.6 (SCK)
/SPI_IO2: R8.2, U1.55 (IOR14B/SSPI_CS_N/D0), U4.3 (SIO2), U5.3 (~WP/IO2)
/SPI_IO3: R10.2, U1.56 (IOR14A/SO/D1), U4.7 (SIO3), U5.7 (~HOLD/IO3)
/SPI_MISO_IO1: U1.62 (IOR11A/MI/D7), U4.2 (SO/SIO), U5.2 (SO/IO1)
/SPI_MOSI_IO0: J_DISPLAY1.3, U1.61 (IOR11B/MO/D6), U4.5 (SI/SIO), U5.5 (SI/IO0)
GND: C1.2, C2.2, C3.2, C4.2, C5.2, C7.2, C8.2, C9.2, C11.2, C12.2, C13.2, C14.2, C15.2, C16.2, C17.2, C18.2, C19.2, C20.2, C21.2, C22.2, C23.2, D1.5, D2.5, D3.5, D4.5, D5.5, D6.5, D7.5, D8.5, D9.5, D11.5, J_DISPLAY1.1, J_DISPLAY1.8, J_DISPLAY1.12, J_DISPLAY1.MP (MountPin), J_EXT1.8, J_EXT1.11, J_EXT1.14, J_EXT1.17, J_EXT1.20, J_EXT1.23, J_EXT1.MP (MountPin), J_JTAG1.5, J_JTAG1.7, LED_DONE1.1 (K), R3.2, R5.2, R6.2, R11.2, R12.2, R15.2, U1.2 (VSS), U1.21 (VSS), U1.24 (VSS), U1.43 (VSS), U1.46 (VSS), U1.65 (VSS), U1.88 (IOT5A/MODE0), U1.89 (EXP), U2.3 (GND), U3.2 (GND), U4.4 (VSS), U5.4 (GND), U6.3 (GND), X1.2 (GND)
LINE: C1.1, C5.1, D1.2, D2.2, D3.2, D4.2, D5.2, D6.2, D7.2, D8.2, D9.2, D11.2, U2.2 (VI), U3.1 (VIN), U3.3 (EN), U6.1 (VIN), U6.5 (EN)
unnamed: C6.1, U6.4 (BST)
unnamed: C6.2, L1.1, U6.2 (SW)
unnamed: LED_DONE1.2 (A), R1.2
unnamed: R4.2, R5.1, U6.6 (FB)
unnamed: R12.1, U1.57 (IOR13A/FASTRD_N/D3)
unnamed: R14.2, R15.1, U3.4 (ADJ)
